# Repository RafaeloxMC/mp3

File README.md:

# MP3

Oooh, an MP3 player! I wanted to build this myself to be able to distance from my phone and still listen to music (if you want to read my full thoughts, see the section below)!

It features:
- two AUX jacks,
- a battery,
- a screen,
- 6 buttons (plus an additional switch to turn the device on or off),
- a microSD card and
- a microUSB port!

<details>
<summary>My thoughts (click to expand)</summary>
I personally dislike my phone. The aspects of always being connected, the aspects of always having a possibility to get distracted are reasons why I would sometimes prefer to not take my phone with me. But there is one problem when I don't have my phone: How am I supposed to listen to music?
Therefore, my idea is to make my own MP3 player. I want to make it minimalist, yet functional. My goals are the following features:
- It has an own battery
- It has an AUX port (optional but an additional 1/4 inch port)
- It has a battery
- It has a USB-C port for charging the battery and adding files to the MP3 players library
- It has a screen
- It has at least 6 buttons (left & right, up & down, select and back)
The idea is not super polished yet, but I really want to build this. My goal is it, to make the MP3 player so small, that it can fit in your pocket easily without annoying you too much. Without having ever seen or held a Gameboy before, this is the formfactor I am aiming for - at least the formfactor I would imagine a Gameboy to have.
Will I really make this? I am unsure, but I really want to.</details>

## The Building Process
I built this project over various months without ever really finishing it. Often, I just opened KiCad to make super small details. This also is my first somewhat complex CAD project!

## The CAD model

Everything can easily be put together. It should work with only two bottom screws, though some glue may be applied to increase sturdiness.

## Improvements
Found anything that could be improved? Open an issue and let me know!

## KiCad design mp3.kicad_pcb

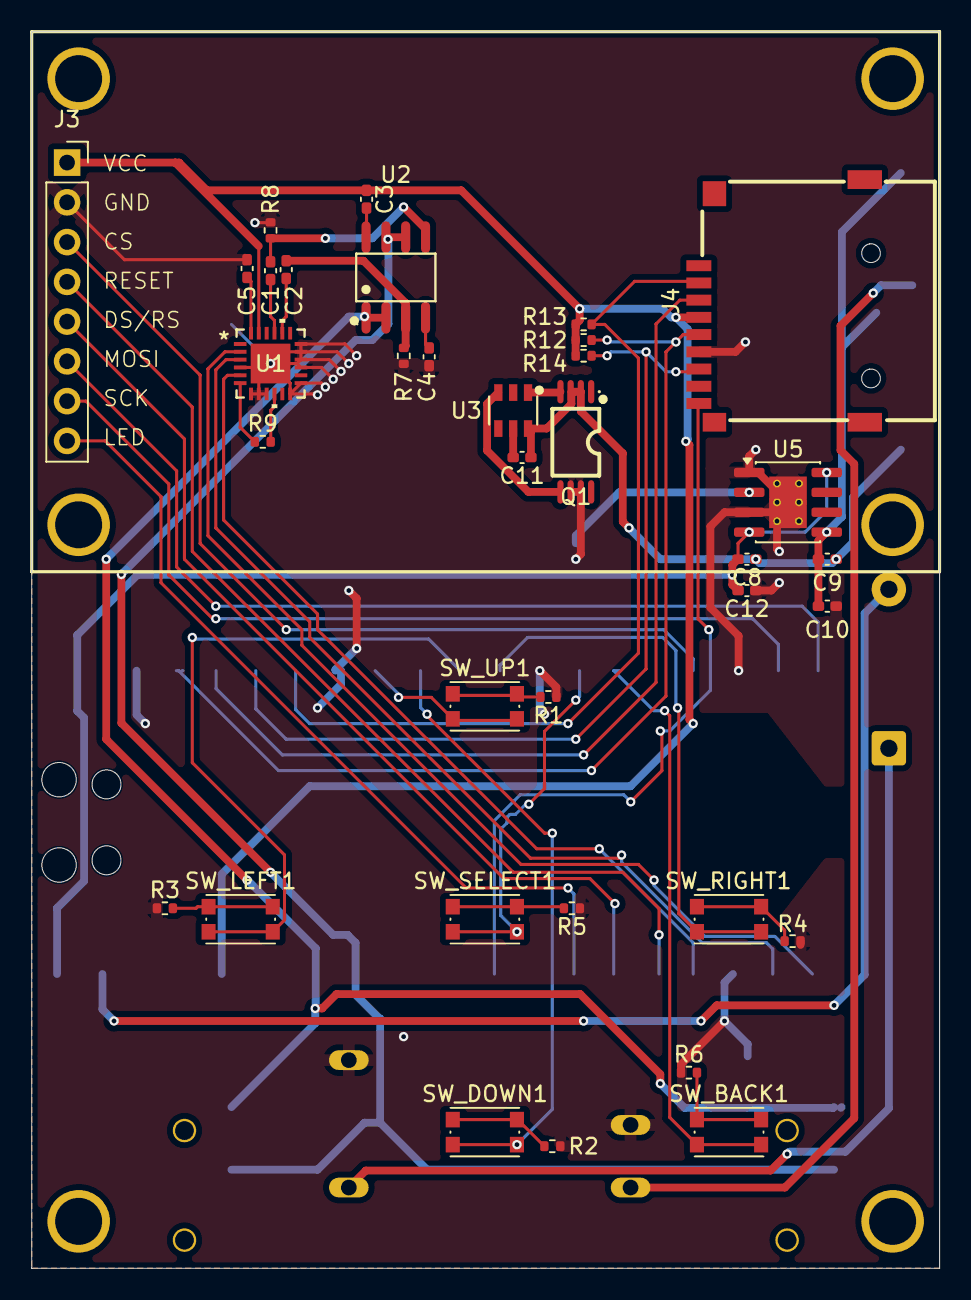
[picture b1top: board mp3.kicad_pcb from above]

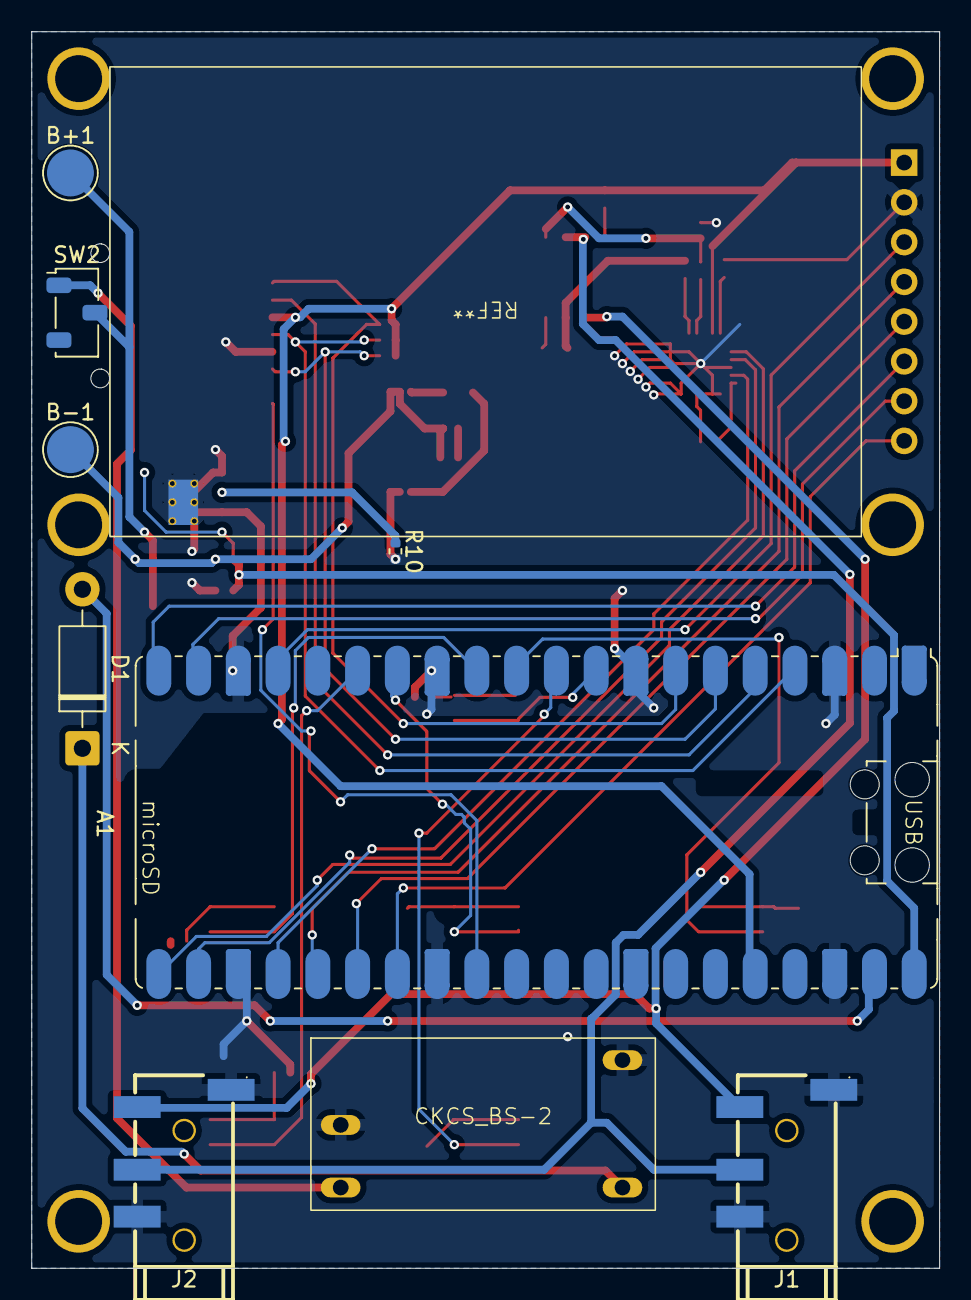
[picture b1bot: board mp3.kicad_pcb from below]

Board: 2 copper layers, 58.0 x 79.0 mm, 44 parts (9 on the bottom side), 49 nets.

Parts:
A1: RaspberryPi_Pico; RaspberryPi_Pico_Common_SMD
B+1: TestPoint; TestPoint_Pad_D3.0mm
B-1: TestPoint; TestPoint_Pad_D3.0mm
C1, C2: 4.7nF; C_0402_1005Metric_Pad0.74x0.62mm_HandSolder
C3, C4: 100nF; C_0402_1005Metric_Pad0.74x0.62mm_HandSolder
C5: 1uF; C_0402_1005Metric_Pad0.74x0.62mm_HandSolder
C8, C9, C10: 10uF; C_0402_1005Metric_Pad0.74x0.62mm_HandSolder
C11, C12: 0.1uF; C_0402_1005Metric_Pad0.74x0.62mm_HandSolder
CKCS_BS-2: CKCS_BS-01
D1: 1N5817; D_DO-41_SOD81_P10.16mm_Horizontal
J1, J2: AudioJack4_Ground; AUDIO-SMD_PJ-320D
J3: Conn_01x08; PinSocket_1x08_P2.54mm_Vertical
J4: Micro_SD_Card_Det1; TF-SMD_XKTF-015-N
Q1: 8205A_C14212; TSSOP-8_L4.4-W3.0-P0.65-LS6.4-BL-2
R1, R2, R3, R4, R5, R6, R9, R12, R13, R14: 10K; R_0402_1005Metric
R7, R8: 1K; R_0402_1005Metric
R10: 1.2K; R_0402_1005Metric
SW2: SW_Nidec_CAS-120A1; Nidec_Copal_CAS-120A
SW_BACK1: SW_Push; SW_Push_1P1T_NO_CK_KMR2
SW_DOWN1: SW_Push; SW_Push_1P1T_NO_CK_KMR2
SW_LEFT1: SW_Push; SW_Push_1P1T_NO_CK_KMR2
SW_RIGHT1: SW_Push; SW_Push_1P1T_NO_CK_KMR2
SW_SELECT1: SW_Push; SW_Push_1P1T_NO_CK_KMR2
SW_UP1: SW_Push; SW_Push_1P1T_NO_CK_KMR2
U1: XTAD5142IRGER; VQFN24_RGE-N_TEX
U2: MCP6002-xSN; SOIC-8_L4.9-W3.9-P1.27-LS6.0-BL
U3: DW01A_C351410; SOT-23-6_L2.9-W1.6-P0.95-LS2.8-BL
U5: TP4056-42-ESOP8; SOIC-8-1EP_3.9x4.9mm_P1.27mm_EP2.41x3.3mm_ThermalVias

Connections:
+BATT: B+1.1 (1_1), C9.1, C10.1, SW2.2 (B), U5.5 (BAT)
-BATT: B-1.1 (1_1), C8.1, C9.2, C11.1, Q1.2 (S1), Q1.3 (S1), U3.6 (GND)
/BTN_BACK: A1.15 (GPIO11), SW_BACK1.2
/BTN_DOWN: A1.10 (GPIO7), SW_DOWN1.2
/BTN_LEFT: A1.11 (GPIO8), SW_LEFT1.2
/BTN_RIGHT: A1.12 (GPIO9), SW_RIGHT1.2
/BTN_SELECT: A1.14 (GPIO10), SW_SELECT1.2
/BTN_UP: A1.9 (GPIO6), SW_UP1.2
/CKCS_IN: CKCS_BS-2.1 (VIN), SW2.1 (C)
/Pico_3V3: A1.36 (3V3), C3.1, J3.1, J4.4 (VDD), R12.1, R13.1, R14.1, U1.23 (AVDD)
/Pico_I2S_FSYNC: A1.22 (GPIO17), U1.3 (FSYNC)
/Pico_I2S_SCK: A1.21 (GPIO16), U1.2 (BCLK)
/Pico_I2S_SD: A1.24 (GPIO18), U1.5 (DIN)
/Pico_VBUS: A1.40 (VBUS), C8.2, C12.2, U5.4 (V_{CC}), U5.8 (CE)
/Pico_VSYS: CKCS_BS-2.3 (VOUT), D1.1 (K)
/SCREEN_CS: A1.17 (GPIO13), J3.3
/SCREEN_DS_RS: A1.26 (GPIO20), J3.5
/SCREEN_LED: A1.27 (GPIO21), J3.8
/SCREEN_RESET: A1.25 (GPIO19), J3.4
/SCREEN_SCK: A1.19 (GPIO14), J3.7
/SCREEN_SDI_MOSI: A1.20 (GPIO15), J3.6
/SD_CLK: A1.4 (GPIO2), J4.5 (CLK), R12.2
/SD_CS: A1.7 (GPIO5), J4.2 (DAT3/CD), R13.2
/SD_DET: A1.29 (GPIO22), J4.9 (DET)
/SD_MISO: A1.6 (GPIO4), J4.7 (DAT0), R14.2
/SD_MOSI: A1.5 (GPIO3), J4.3 (CMD)
GND: A1.3 (GND), A1.8 (GND), A1.13 (GND), A1.18 (GND), A1.23 (GND), A1.28 (GND), A1.38 (GND), C4.2, C5.1, C10.2, C12.1, CKCS_BS-2.2 (GND), CKCS_BS-2.4 (GND), J1.1, J1.2, J2.1, J2.2, J3.2, J4.6 (VSS), Q1.6 (S2), Q1.7 (S2), R1.1, R2.1, R3.1, R4.1, R5.1, R6.1, R7.1, R8.2, R10.2, U1.4 (MD6), U1.7 (MD1), U1.8 (MD2), U1.9 (MD3), U1.12 (MD5), U1.13 (MD0), U1.15 (VSSA), U1.16 (VSSA), U1.17 (VSSA), U1.18 (VSSA), U1.25 (EPAD), U5.1 (TEMP), U5.3 (GND), U5.9 (EPAD)
unnamed: A1.39 (VSYS), D1.2 (A)
unnamed: Q1.4 (G1), U3.1 (OD)
unnamed: Q1.5 (G2), U3.3 (OC)
unnamed: R1.2, SW_UP1.1
unnamed: R2.2, SW_DOWN1.1
unnamed: R3.2, SW_LEFT1.1
unnamed: R4.2, SW_RIGHT1.1
unnamed: R5.2, SW_SELECT1.1
unnamed: R6.2, SW_BACK1.1
unnamed: R9.1, U1.6 (IOVDD)
unnamed: R9.2, U1.10 (MD4)
unnamed: C2.1, U1.20 (OUT1P)
unnamed: C1.2, U1.21 (OUT2P)
unnamed: C5.2, U1.24 (VREF)
unnamed: C2.2, R7.2, U2.3 (+)
unnamed: J1.4, J2.4, U2.1, U2.2 (-)
unnamed: C1.1, R8.1, U2.5 (+)
unnamed: J1.3, J2.3, U2.6 (-), U2.7
unnamed: C3.2, U2.8 (V+)
unnamed: C4.1, U2.4 (V-)
unnamed: C11.2, U3.5 (VCC)
unnamed: R10.1, U5.2 (PROG)

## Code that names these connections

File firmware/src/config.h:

#ifndef CONFIG_H
#define CONFIG_H

#define PIN_SD_SCK 2
#define PIN_SD_MOSI 3
#define PIN_SD_MISO 4
#define PIN_SD_CS 5
#define SD_SPI_PORT spi0
#define SD_BAUD_RATE_HZ (20 * 1000 * 1000)
#define PIN_SD_DET 22
#define SD_DET_PRESENT_VALUE 0

#define PIN_BTN_UP 6
#define PIN_BTN_DOWN 7
#define PIN_BTN_LEFT 8
#define PIN_BTN_RIGHT 9
#define PIN_BTN_SELECT 10
#define PIN_BTN_BACK 11

#define PIN_SCREEN_MISO 12
#define PIN_SCREEN_CS 13
#define PIN_SCREEN_SCK 14
#define PIN_SCREEN_MOSI 15
#define SCREEN_SPI_PORT spi1
#define SCREEN_SPI_BAUD_RATE_HZ (32 * 1000 * 1000)
#define PIN_SCREEN_RESET 19
#define PIN_SCREEN_DC 20
#define PIN_SCREEN_BACKLIGHT 21

#define PIN_I2S_BCLK 16
#define PIN_I2S_LRCLK 17
#define PIN_I2S_DOUT 18

#define SCREEN_WIDTH 128
#define SCREEN_HEIGHT 160

#define AUDIO_SAMPLE_RATE_MAX 48000
#define AUDIO_CHANNELS 2

#define VOLUME_MIN 0
#define VOLUME_MAX 100
#define VOLUME_DEFAULT 60

#define COVER_ART_MAX_SIZE 96

#define BUTTON_DEBOUNCE_MS 30
#define BUTTON_REPEAT_START_MS 400
#define BUTTON_REPEAT_INTERVAL_MS 120

#endif

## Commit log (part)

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2026-04-22 Add voltage booster, optimizations
2026-04-22 Full re-routing
2026-04-23 Fix diode direction
2026-04-23 Add new battery management system
2026-04-27 Move Pico and audio jacks closer to PCB border
